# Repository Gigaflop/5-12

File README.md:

# 5-12
A 5x12 ortho with a full grid layout and 2x2u spacebars. Fancier name in the works.

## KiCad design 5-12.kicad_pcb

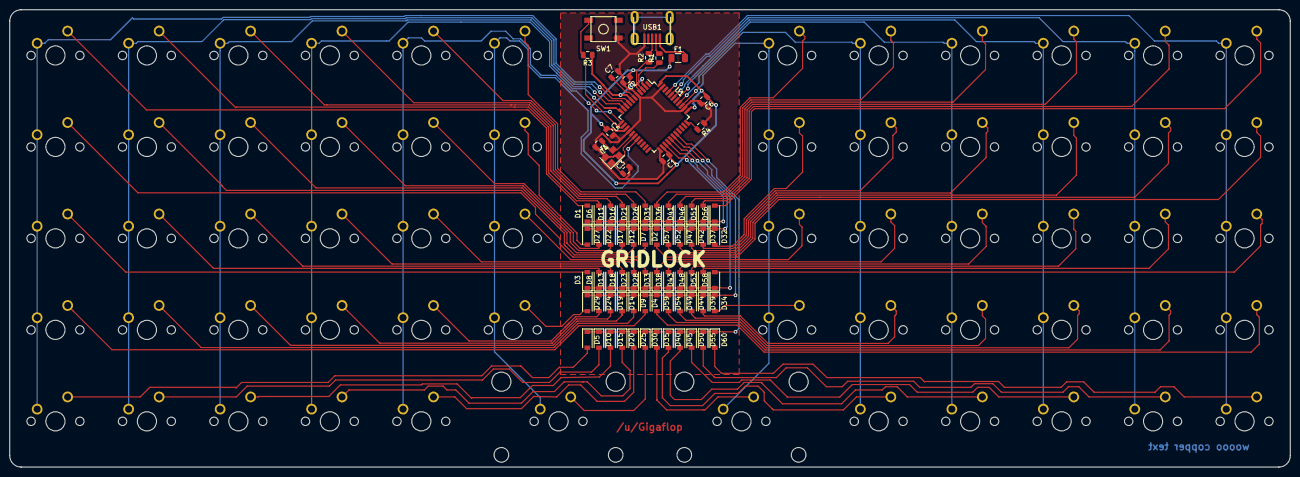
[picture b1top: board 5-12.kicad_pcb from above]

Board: 2 copper layers, 266.7 x 95.2 mm, 136 parts (0 on the bottom side), 89 nets.

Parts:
C1, C2, C5: 0.1uF; C_0805_2012Metric
C3, C4: 22pF; C_0805_2012Metric
C6: 10uF; C_0805_2012Metric
C7: 1uF; C_0805_2012Metric
D1, D2, D3, D4, D5, D6, D7, D8, D9, D10, D11, D12, D13, D14, D15, D16, D17, D18, D19, D20, D21, D22, D23, D24, D25, D26, D27, D28, D29, D30, D31, D32, D33, D34, D35, D36, D37, D38, D39, D40, D41, D42, D43, D44, D45, D46, D47, D48, D49, D50, D51, D52, D53, D54, D55, D56, D57, D58, D59, D60: SOD-123; D_SOD-123
F1: 500mA; Fuse_1206_3216Metric
MX1, MX2, MX3, MX4, MX5, MX6, MX7, MX8, MX9, MX10, MX11, MX12, MX13, MX14, MX15, MX16, MX17, MX18, MX19, MX20, MX21, MX22, MX23, MX24, MX25, MX26, MX27, MX28, MX29, MX31, MX32, MX33, MX34, MX36, MX37, MX38, MX39, MX40, MX41, MX42, MX43, MX44, MX45, MX46, MX47, MX48, MX49, MX50, MX51, MX52, MX53, MX54, MX55, MX56, MX57, MX58, MX59, MX60: MX-NoLED; MXOnly-1U-NoLED
MX30, MX35: MX-NoLED_2u; MXOnly-2U-ReversedStabilizers-NoLED
R1, R2: 22; R_0805_2012Metric
R3, R4: 10k; R_0805_2012Metric
SW1: SW_Push; SKQG-1155865
U1: ATmega32U4-AU; TQFP-44_10x10mm_P0.8mm
USB1: Molex-0548190589
Y1: 16MHz; Crystal_SMD_3225-4Pin_3.2x2.5mm

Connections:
+5V: C1.1, C2.1, C5.1, C6.1, F1.1, R3.1, U1.2, U1.7, U1.14, U1.24, U1.34, U1.44
Col0: MX1.1, MX2.1, MX3.1, MX4.1, MX5.1, U1.8
Col1: MX6.1, MX7.1, MX8.1, MX9.1, MX10.1, U1.9
Col2: MX11.1, MX12.1, MX13.1, MX14.1, MX15.1, U1.10
Col3: MX16.1, MX17.1, MX18.1, MX19.1, MX20.1, U1.11
Col4: MX21.1, MX22.1, MX23.1, MX24.1, MX25.1, U1.12
Col5: MX26.1, MX27.1, MX28.1, MX29.1, MX30.1, U1.18
Col6: MX31.1, MX32.1, MX33.1, MX34.1, MX35.1, U1.36
Col7: MX36.1, MX37.1, MX38.1, MX39.1, MX40.1, U1.37
Col8: MX41.1, MX42.1, MX43.1, MX44.1, MX45.1, U1.38
Col9: MX46.1, MX47.1, MX48.1, MX49.1, MX50.1, U1.39
Col10: MX51.1, MX52.1, MX53.1, MX54.1, MX55.1, U1.40
Col11: MX56.1, MX57.1, MX58.1, MX59.1, MX60.1, U1.41
D+: R2.2, USB1.3
D-: R1.2, USB1.4
GND: C1.2, C2.2, C3.2, C4.2, C5.2, C6.2, C7.2, R4.1, SW1.1, U1.5, U1.15, U1.23, U1.35, U1.43, USB1.1, Y1.2, Y1.4
unnamed: C3.1, U1.17, Y1.1
unnamed: C4.1, U1.16, Y1.3
unnamed: C7.1, U1.6
unnamed: D1.2, MX1.2
unnamed: D2.2, MX2.2
unnamed: D3.2, MX3.2
unnamed: D4.2, MX4.2
unnamed: D5.2, MX5.2
unnamed: D6.2, MX6.2
unnamed: D7.2, MX7.2
unnamed: D8.2, MX8.2
unnamed: D9.2, MX9.2
unnamed: D10.2, MX10.2
unnamed: D11.2, MX11.2
unnamed: D12.2, MX12.2
unnamed: D13.2, MX13.2
unnamed: D14.2, MX14.2
unnamed: D15.2, MX15.2
unnamed: D16.2, MX16.2
unnamed: D17.2, MX17.2
unnamed: D18.2, MX18.2
unnamed: D19.2, MX19.2
unnamed: D20.2, MX20.2
unnamed: D21.2, MX21.2
unnamed: D22.2, MX22.2
unnamed: D23.2, MX23.2
unnamed: D24.2, MX24.2
unnamed: D25.2, MX25.2
unnamed: D26.2, MX26.2
unnamed: D27.2, MX27.2
unnamed: D28.2, MX28.2
unnamed: D29.2, MX29.2
unnamed: D30.2, MX30.2
unnamed: D31.2, MX31.2
unnamed: D32.2, MX32.2
unnamed: D33.2, MX33.2
unnamed: D34.2, MX34.2
unnamed: D35.2, MX35.2
unnamed: D36.2, MX36.2
unnamed: D37.2, MX37.2
unnamed: D38.2, MX38.2
unnamed: D39.2, MX39.2
unnamed: D40.2, MX40.2
unnamed: D41.2, MX41.2
unnamed: D42.2, MX42.2
unnamed: D43.2, MX43.2
unnamed: D44.2, MX44.2
unnamed: D45.2, MX45.2
unnamed: D46.2, MX46.2
unnamed: D47.2, MX47.2
unnamed: D48.2, MX48.2
unnamed: D49.2, MX49.2
unnamed: D50.2, MX50.2
unnamed: D51.2, MX51.2
unnamed: D52.2, MX52.2
unnamed: D53.2, MX53.2
unnamed: D54.2, MX54.2
unnamed: D55.2, MX55.2
unnamed: D56.2, MX56.2
unnamed: D57.2, MX57.2
unnamed: D58.2, MX58.2
unnamed: D59.2, MX59.2
unnamed: D60.2, MX60.2
unnamed: R1.1, U1.3
unnamed: R2.1, U1.4
unnamed: R3.2, SW1.2, U1.13
unnamed: R4.2, U1.33
Row0: D1.1, D6.1, D11.1, D16.1, D21.1, D26.1, D31.1, D36.1, D41.1, D46.1, D51.1, D56.1, U1.25
Row1: D2.1, D7.1, D12.1, D17.1, D22.1, D27.1, D32.1, D37.1, D42.1, D47.1, D52.1, D57.1, U1.26
Row2: D3.1, D8.1, D13.1, D18.1, D23.1, D28.1, D33.1, D38.1, D43.1, D48.1, D53.1, D58.1, U1.27
Row3: D4.1, D9.1, D14.1, D19.1, D24.1, D29.1, D34.1, D39.1, D44.1, D49.1, D54.1, D59.1, U1.28
Row4: D5.1, D10.1, D15.1, D20.1, D25.1, D30.1, D35.1, D40.1, D45.1, D50.1, D55.1, D60.1, U1.29
VCC: F1.2, USB1.5

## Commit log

2020-05-13 added gitignore
2020-05-13 add kicad init and submodules
2020-05-13 added libs form submodules into kicad
2020-05-13 tutorial progress up to decoupling caps
2020-05-14 Finishjed MCU zone on schematic
2020-05-14 Added USB and uncpnnected switch matrix
2020-05-14 added r, c tags for matrix
2020-05-14 Added mappings to footprints
2020-05-19 Laid out switch matrix
2020-05-19 Partially placed diodes
2020-05-21 swapped MX footprints for NOLED version
2020-05-21 initial, normal diode placement done
2020-05-21 Completed initial layout for MCU zone
2020-05-22 Initial usb placement
2020-05-23 initial placement of usb components, rotation of mcu, replacement and adjustment of MCU group
2020-05-23 Wired mcu and usb
2020-05-23 Added col traces between rows
2020-05-23 Routed left half of bottom row
2020-05-23 Finished routing bottom row to diode bank
2020-05-23 moved diodes of right side r4 into bank
2020-05-24 Moved left side of R2 into bank, did partial routing from bank back to switches to test the fit
2020-05-24 finished left diode banks and their initial routes
2020-05-24 Finished initial routing of left switches to left diode banks
2020-05-24 Positioned remainder of diode banks
2020-05-24 Reordered a right row diode bank for proper arrangement
2020-05-24 morning transfer
2020-05-24 Finished routing switches to diode banks
2020-05-24 Finished pre-routing of row, col lines ahead into buses
2020-05-26 Genned production files, made zip
